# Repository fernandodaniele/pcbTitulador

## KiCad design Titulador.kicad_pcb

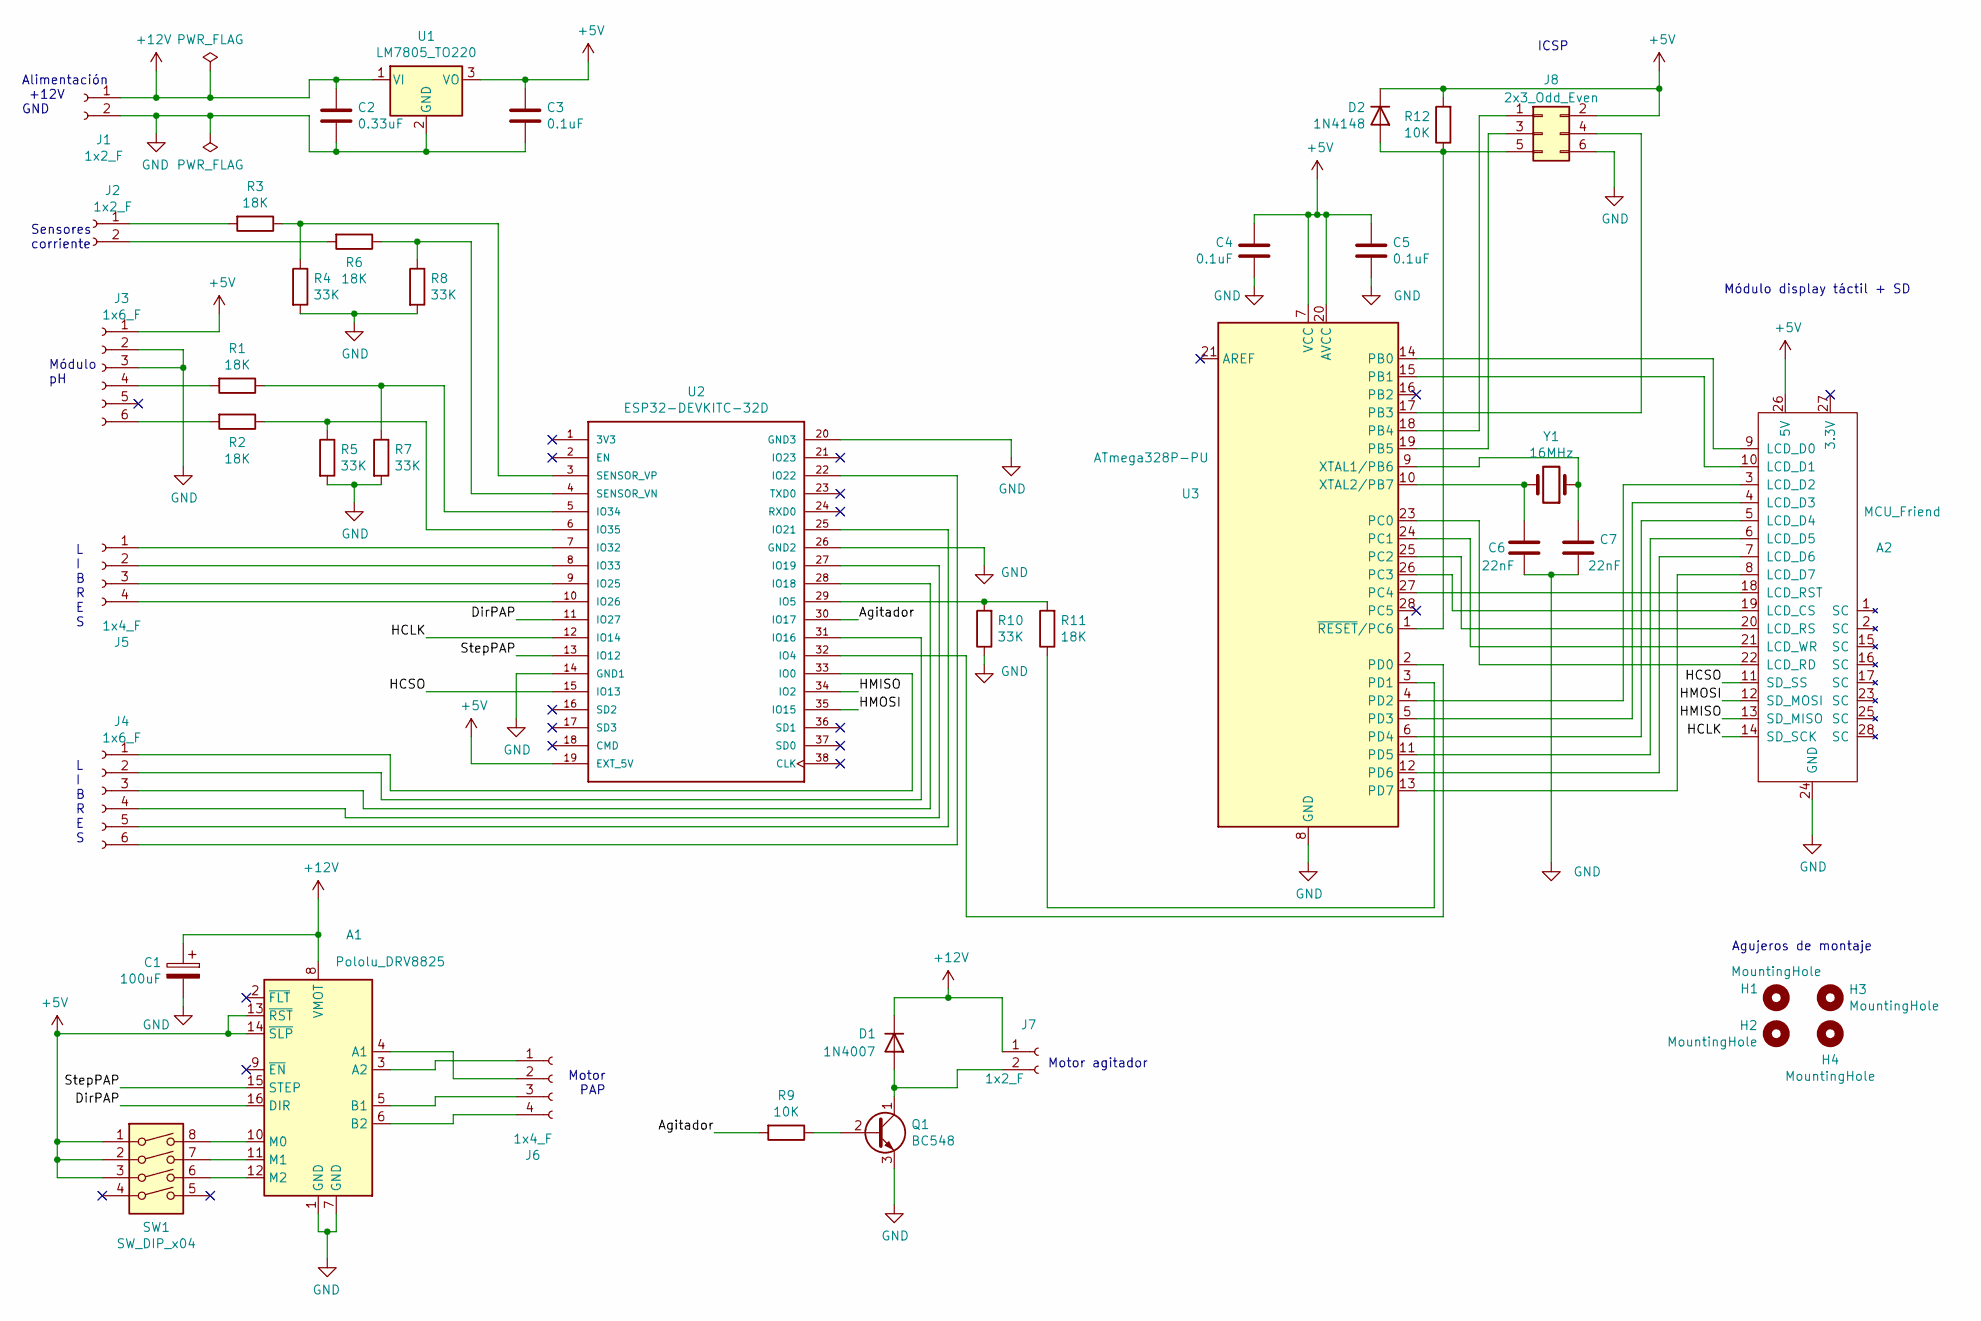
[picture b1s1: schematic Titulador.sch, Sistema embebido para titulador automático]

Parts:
A1: Pololu_DRV8825; Pololu_Breakout-16_15.2x20.3mm
A2: MCU_Friend; MCUFriend
C1: 100uF; CP_Radial_D7.5mm_P2.50mm
C2: 0.33uF; C_Axial_L5.1mm_D3.1mm_P7.50mm_Horizontal
C3, C4, C5: 0.1uF; C_Axial_L5.1mm_D3.1mm_P7.50mm_Horizontal
C6, C7: 22nF; C_Axial_L5.1mm_D3.1mm_P7.50mm_Horizontal
D1: 1N4007; D_A-405_P7.62mm_Horizontal
D2: 1N4148; D_A-405_P7.62mm_Horizontal
H1, H2, H3, H4: MountingHole; MountingHole_3mm
J1, J2, J7: 1x2_F; PinSocket_1x02_P2.54mm_Vertical
J3: 1x6_F; PinSocket_1x06_P2.54mm_Vertical
J4: 1x6_F; PinHeader_1x06_P2.54mm_Vertical
J5, J6: 1x4_F; PinSocket_1x04_P2.54mm_Vertical
J8: 2x3_Odd_Even; PinHeader_2x03_P2.54mm_Vertical
Q1: BC548; TO-92L_Wide
R1, R2, R3, R6, R11: 18K; R_Axial_DIN0207_L6.3mm_D2.5mm_P7.62mm_Horizontal
R4, R5, R7, R8, R10: 33K; R_Axial_DIN0207_L6.3mm_D2.5mm_P7.62mm_Horizontal
R9, R12: 10K; R_Axial_DIN0207_L6.3mm_D2.5mm_P7.62mm_Horizontal
SW1: SW_DIP_x04; SW_DIP_SPSTx04_Slide_6.7x11.72mm_W7.62mm_P2.54mm_LowProfile
U1: LM7805_TO220; TO-220F-3_Horizontal_TabDown
U2: ESP32-DEVKITC-32D; MODULE_ESP32-DEVKITC-32D
U3: ATmega328P-PU; DIP-28_W7.62mm
Y1: 16MHz; Crystal_HC18-U_Vertical

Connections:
+5V: A1.13 (~RST), A1.14 (~SLP), A2.26 (5V), C3.1, C4.1, C5.1, D2.1 (K), J3.1, J8.2, R12.2, SW1.1, SW1.2, SW1.3, U1.3 (VO), U2.19 (EXT_5V), U3.7 (VCC), U3.20 (AVCC)
+12V: A1.8 (VMOT), C1.1, C2.1, D1.1 (K), J1.1, J7.1, U1.1 (VI)
/Agitador: R9.2, U2.30 (IO17)
/DirPAP: A1.16 (DIR), U2.11 (IO27)
/HCLK: A2.14 (SD_SCK), U2.12 (IO14)
/HCSO: A2.11 (SD_SS), U2.15 (IO13)
/HMISO: A2.13 (SD_MISO), U2.34 (IO2)
/HMOSI: A2.12 (SD_MOSI), U2.35 (IO15)
/StepPAP: A1.15 (STEP), U2.13 (IO12)
GND: A1.1 (GND), A1.7 (GND), A2.24 (GND), C1.2, C2.2, C3.2, C4.2, C5.2, C6.1, C7.2, J1.2, J3.2, J3.3, J8.6, Q1.3 (E), R4.2, R5.2, R7.2, R8.2, R10.1, U1.2 (GND), U2.14 (GND1), U2.20 (GND3), U2.26 (GND2), U3.8 (GND), U3.22 (GND)
unnamed: A1.3 (A2), J6.1
unnamed: A1.4 (A1), J6.2
unnamed: A1.5 (B1), J6.3
unnamed: A1.6 (B2), J6.4
unnamed: A1.10 (M0), SW1.8
unnamed: A1.11 (M1), SW1.7
unnamed: A1.12 (M2), SW1.6
unnamed: A2.3 (LCD_D2), U3.4 (PD2)
unnamed: A2.4 (LCD_D3), U3.5 (PD3)
unnamed: A2.5 (LCD_D4), U3.6 (PD4)
unnamed: A2.6 (LCD_D5), U3.11 (PD5)
unnamed: A2.7 (LCD_D6), U3.12 (PD6)
unnamed: A2.8 (LCD_D7), U3.13 (PD7)
unnamed: A2.9 (LCD_D0), U3.14 (PB0)
unnamed: A2.10 (LCD_D1), U3.15 (PB1)
unnamed: A2.18 (LCD_RST), U3.27 (PC4)
unnamed: A2.19 (LCD_CS), U3.26 (PC3)
unnamed: A2.20 (LCD_RS), U3.25 (PC2)
unnamed: A2.21 (LCD_WR), U3.24 (PC1)
unnamed: A2.22 (LCD_RD), U3.23 (PC0)
unnamed: C6.2, U3.10 (XTAL2/PB7), Y1.2
unnamed: C7.1, U3.9 (XTAL1/PB6), Y1.1
unnamed: D1.2 (A), J7.2, Q1.1 (C)
unnamed: D2.2 (A), J8.5, R12.1, U3.1 (~RESET~/PC6)
unnamed: J2.1, R3.2
unnamed: J2.2, R6.2
unnamed: J3.4, R1.2
unnamed: J3.6, R2.2
unnamed: J4.1, U2.33 (IO0)
unnamed: J4.2, U2.31 (IO16)
unnamed: J4.3, U2.28 (IO18)
unnamed: J4.4, U2.27 (IO19)
unnamed: J4.5, U2.25 (IO21)
unnamed: J4.6, U2.22 (IO22)
unnamed: J5.1, U2.7 (IO32)
unnamed: J5.2, U2.8 (IO33)
unnamed: J5.3, U2.9 (IO25)
unnamed: J5.4, U2.10 (IO26)
unnamed: J8.1, U3.18 (PB4)
unnamed: J8.3, U3.19 (PB5)
unnamed: J8.4, U3.17 (PB3)
unnamed: Q1.2 (B), R9.1
unnamed: R1.1, R7.1, U2.5 (IO34)
unnamed: R2.1, R5.1, U2.6 (IO35)
unnamed: R3.1, R4.1, U2.3 (SENSOR_VP)
unnamed: R6.1, R8.1, U2.4 (SENSOR_VN)
unnamed: R10.2, R11.2, U2.29 (IO5)
unnamed: R11.1, U3.3 (PD1)
unnamed: U2.32 (IO4), U3.2 (PD0)

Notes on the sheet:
Alimentación +12V GND
Módulo pH
L I B R E S
Motor agitador
Módulo display táctil + SD
Sensores corriente
Agujeros de montaje
Motor PAP
ICSP

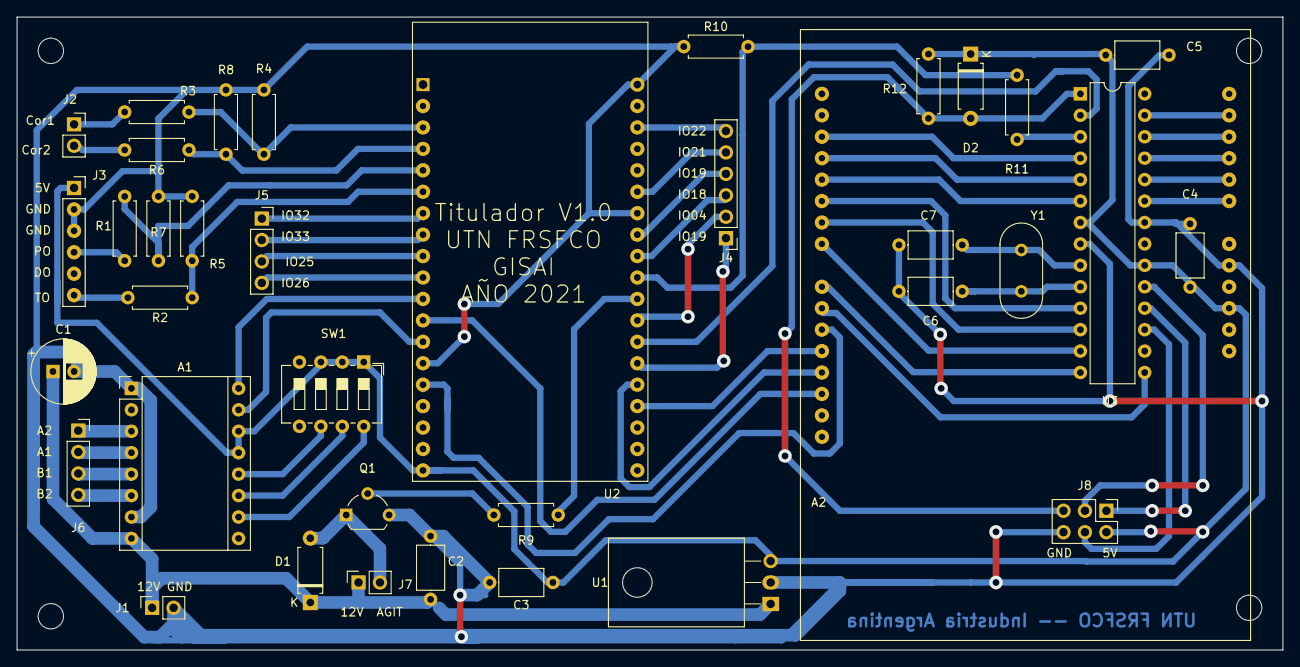
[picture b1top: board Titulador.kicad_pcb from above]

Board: 2 copper layers, 150.0 x 75.0 mm, 41 parts (0 on the bottom side), 59 nets.

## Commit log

2020-09-08 Propuesta TP DCI
2020-10-09 Para correccion de companiero
2020-10-09 se agregan pinout
2020-10-23 Se agrega pcb
2021-02-03 Se actualiza esquematico con atmega328pu
2021-02-09 Se finaliza primera version esquematico y PCB
2021-02-11 Correcciones menores
